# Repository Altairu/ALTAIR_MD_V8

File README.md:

# ALTAIR_MD_V8
**High-Power Isolated Motor Driver Board**

<blockquote class="twitter-tweet"><p lang="ja" dir="ltr">NEWもたどら <a href="https://t.co/xIfIAs8RRS">pic.twitter.com/xIfIAs8RRS</a></p>&mdash; -Altair- (@Flying___eagle) <a href="https://twitter.com/Flying___eagle/status/2016806401205797079?ref_src=twsrc%5Etfw">January 29, 2026</a></blockquote> 

## 概要 (Overview)
**ALTAIR_MD_V8** は、STMicroelectronics製の車載用高出力フルブリッジドライバー **VNH5019A-E** を搭載したDCモータードライバーモジュールです。

制御信号ラインにデジタルアイソレータ (**ADuM121N**) を採用することで、モーター駆動系（24V系）とマイコン制御系（3.3V/5V系）のGNDを完全に分離（絶縁）しています。

## 特徴 (Features)
*   **高出力駆動**: 連続12A / 最大30A の大電流駆動が可能（VNH5019A-E仕様に基づく）。
*   **完全絶縁設計**: Analog Devices製 デジタルアイソレータ ADuM121N を採用し、ロジック側とパワー側のGNDを分離。
*   **広範囲なロジック電圧**: 1.8V ～ 5V のロジック入力に対応（マイコンを選ばない設計）。
*   **保護機能**:
    *   過電圧・低電圧シャットダウン
    *   過熱保護 (Thermal Shutdown)
    *   電流センシング機能 (Current Sense Output)

## 仕様 (Specifications)

| 項目 | 仕様 | 備考 |
| :--- | :--- | :--- |
| **メインドライバー** | STMicroelectronics VNH5019A-E | AEC-Q100準拠 (車載グレード) |
| **絶縁素子** | Analog Devices ADuM121N | 2ch デジタルアイソレータ (計2個使用) |
| **入力電源電圧** | DC 5.5V ～ 24V | パワー側電源 (VCC/VBAT) |
| **ロジック入力電圧** | DC 1.8V ～ 5.5V | マイコン側I/O電圧 |
| **最大出力電流** | 連続 12A / ピーク 30A | 放熱条件に依存 |
| **電流センシング** | アナログ電圧出力 | 1.5kΩ抵抗接続時 (約0.14V/A) |

## 回路図 (Schematic)

### 主な構成
*   **絶縁回路**: マイコンからの制御信号（PWM1, PWM2, ENABLE）は、ADuM121N を介して VNH5019A-E に伝送されます。
*   **電源生成**: 24V入力からオンボードの降圧レギュレータにより、絶縁二次側（ドライバー側）用の5V電源を生成しています。
*   **保護設定**:
    *   **CP (Charge Pump)**: オープン（未接続）
    *   **VBAT**: VCCと短絡（逆接保護MOSFETなし構成のため）
  
## PCB Layout

## インターフェース (Interface)

### 入力ピン (CN1 / マイコン側)
| ピン名 | 機能 | 説明 |
| :--- | :--- | :--- |
| **PWM1** | INA 入力 | モーター回転方向制御 A (正転/逆転) |
| **PWM2** | INB 入力 | モーター回転方向制御 B (正転/逆転) |
| **SD** | 動作許可 (PWM Pin) | **HIGH**: 動作許可, **LOW**: フリーラン停止 (全OFF) |
| **GND** | ロジックGND | マイコン側のGNDと接続 |

### 出力ピン (CN2 / モーター・電源側)
| ピン名 | 機能 | 説明 |
| :--- | :--- | :--- |
| **+24V** | 電源入力 (+) | モーター用メイン電源 (最大24V) |
| **GND_P** | パワーGND (-) | 電源およびモーターのグラウンド |
| **OUT A** | モーター出力 A | モーターの端子へ接続 |
| **OUT B** | モーター出力 B | モーターの端子へ接続 |
| **CS** | 電流センス出力 | 電流値に応じたアナログ電圧を出力 (ADCで読取可) |

## 制御ロジック (Truth Table)

VNH5019A-E の仕様に基づく真理値表です。
**SD (Shutdown/Enable)** ピンが HIGH の時のみモーターが駆動します。

| SD (Enable) | PWM1 (INA) | PWM2 (INB) | OUT A | OUT B | 動作モード |
| :---: | :---: | :---: | :---: | :---: | :--- |
| **L** | X | X | OPEN | OPEN | **フリーラン停止 (All OFF)** |
| **H** | **H** | **L** | **H** | **L** | **正転 (CW)** |
| **H** | **L** | **H** | **L** | **H** | **逆転 (CCW)** |
| **H** | **L** | **L** | **L** | **L** | **ブレーキ (GNDショート)** |
| **H** | **H** | **H** | **H** | **H** | **ブレーキ (VCCショート)** |

*   速度制御を行う場合は、回転方向に応じて PWM1 または PWM2 に PWM信号を入力し、もう片方を LOW にしてください。
*   惰性走行させたい場合は、SDピンを LOW にしてください。

## 電流センシング (Current Sense)
CSピンからは、モーター電流に比例した電流が出力されます。基板上の 1.5kΩ 抵抗により電圧に変換されています。

*   **計算式**: $V_{CS} \approx \frac{I_{OUT}}{K} \times 1.5k\Omega$
*   **K係数**: Typ. 7000 (VNH5019A-E datasheet)
*   **目安**: モーター電流 1A あたり 約 0.21V の出力

## 組み立て・使用上の注意
1.  **電源投入順序**: 
    ロジック回路(ADuM121N)は一次側・二次側両方に電源が必要です。+24V電源を投入することで二次側5Vが生成され、システムが動作可能になります。
2.  **放熱**:
    30A近い電流を流す場合、IC底面の放熱パッド（ヒートスラッグ）への熱設計が重要です。必要に応じてヒートシンクや強制空冷を行ってください。
3.  **配線**:
    電源ラインとモーター出力ラインは、大電流が流れるため可能な限り太く短い配線を使用してください。

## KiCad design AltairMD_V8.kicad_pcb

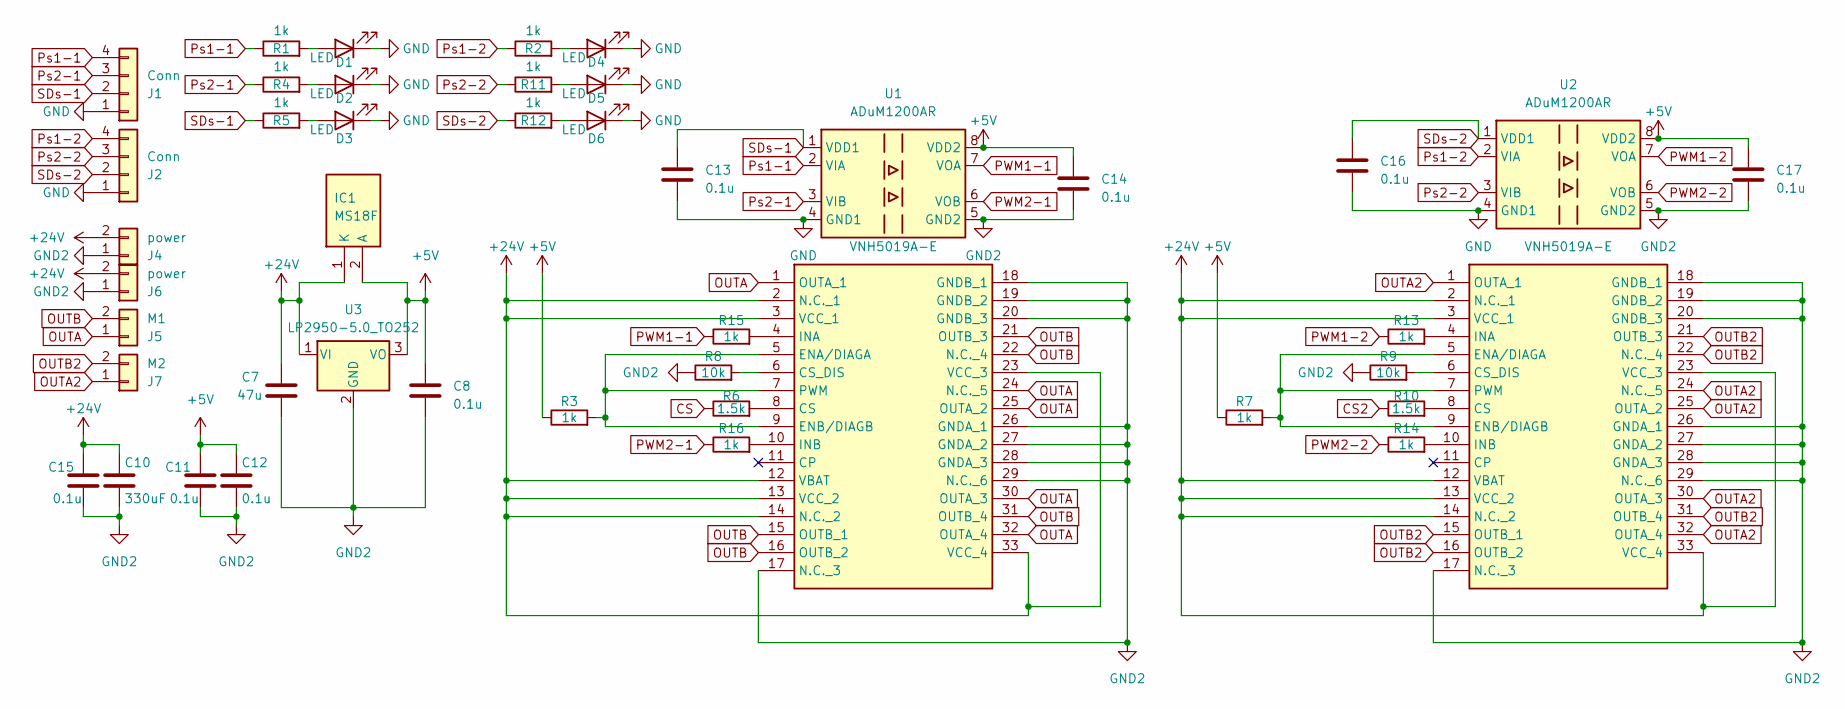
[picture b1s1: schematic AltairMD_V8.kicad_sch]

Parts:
C7: 47u; C_0603_1608Metric
C8, C11, C12, C13, C14, C15, C16, C17: 0.1u; C_0603_1608Metric
C10: 330uF; CP_Elec_10x10
D1, D2, D3, D4, D5, D6: LED; LED_0603_1608Metric
IC1: MS18F; SODFL4725X110N; Manufacturer_Part_Number MS18F
IC2, IC3: VNH5019A-E; VNH5019AE; Manufacturer_Part_Number VNH5019A-E; Mouser Part Number 511-VNH5019A-E
J1, J2: Conn; JST_XA_S04B-XASK-1_1x04_P2.50mm_Horizontal
J4, J6: power; AMASS_XT30PW-M_1x02_P2.50mm_Horizontal
J5: M1; AMASS_XT30PW-F_1x02_P2.50mm_Horizontal
J7: M2; AMASS_XT30PW-F_1x02_P2.50mm_Horizontal
R1, R2, R3, R4, R5, R7, R11, R12, R13, R14, R15, R16: 1k; R_0603_1608Metric
R6, R10: 1.5k; R_0603_1608Metric
R8, R9: 10k; R_0603_1608Metric
U1, U2: ADuM1200AR; SOIC-8_3.9x4.9mm_P1.27mm
U3: LP2950-5.0_TO252; TO-252-2

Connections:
+5V: C8.1, C11.1, C12.1, C14.1, C17.1, IC1.2 (A), R3.1, R7.1, U1.8 (VDD2), U2.8 (VDD2), U3.3 (VO)
+24V: C7.1, C10.1, C15.1, IC1.1 (K), IC2.2 (N.C._1), IC2.3 (VCC_1), IC2.12 (VBAT), IC2.13 (VCC_2), IC2.14 (N.C._2), IC2.23 (VCC_3), IC2.33 (VCC_4), IC3.2 (N.C._1), IC3.3 (VCC_1), IC3.12 (VBAT), IC3.13 (VCC_2), IC3.14 (N.C._2), IC3.23 (VCC_3), IC3.33 (VCC_4), J4.2, J6.2, U3.1 (VI)
CS: R6.1
CS2: R10.1
GND: C13.2, C16.2, D1.1 (K), D2.1 (K), D3.1 (K), D4.1 (K), D5.1 (K), D6.1 (K), J1.1, J2.1, U1.4 (GND1), U2.4 (GND1)
GND2: C7.2, C8.2, C10.2, C11.2, C12.2, C14.2, C15.2, C17.2, IC2.17 (N.C._3), IC2.18 (GNDB_1), IC2.19 (GNDB_2), IC2.20 (GNDB_3), IC2.26 (GNDA_1), IC2.27 (GNDA_2), IC2.28 (GNDA_3), IC2.29 (N.C._6), IC3.17 (N.C._3), IC3.18 (GNDB_1), IC3.19 (GNDB_2), IC3.20 (GNDB_3), IC3.26 (GNDA_1), IC3.27 (GNDA_2), IC3.28 (GNDA_3), IC3.29 (N.C._6), J4.1, J6.1, R8.1, R9.1, U1.5 (GND2), U2.5 (GND2), U3.2 (GND)
unnamed: D1.2 (A), R1.2
unnamed: D2.2 (A), R4.2
unnamed: D3.2 (A), R5.2
unnamed: D4.2 (A), R2.2
unnamed: D5.2 (A), R11.2
unnamed: D6.2 (A), R12.2
unnamed: IC2.8 (CS), R6.2
unnamed: IC2.6 (CS_DIS), R8.2
unnamed: IC2.5 (ENA/DIAGA), IC2.7 (PWM), IC2.9 (ENB/DIAGB), R3.2
unnamed: IC2.4 (INA), R15.2
unnamed: IC2.10 (INB), R16.2
unnamed: IC3.8 (CS), R10.2
unnamed: IC3.6 (CS_DIS), R9.2
unnamed: IC3.5 (ENA/DIAGA), IC3.7 (PWM), IC3.9 (ENB/DIAGB), R7.2
unnamed: IC3.4 (INA), R13.2
unnamed: IC3.10 (INB), R14.2
OUTA: IC2.1 (OUTA_1), IC2.24 (N.C._5), IC2.25 (OUTA_2), IC2.30 (OUTA_3), IC2.32 (OUTA_4), J5.1
OUTA2: IC3.1 (OUTA_1), IC3.24 (N.C._5), IC3.25 (OUTA_2), IC3.30 (OUTA_3), IC3.32 (OUTA_4), J7.1
OUTB: IC2.15 (OUTB_1), IC2.16 (OUTB_2), IC2.21 (OUTB_3), IC2.22 (N.C._4), IC2.31 (OUTB_4), J5.2
OUTB2: IC3.15 (OUTB_1), IC3.16 (OUTB_2), IC3.21 (OUTB_3), IC3.22 (N.C._4), IC3.31 (OUTB_4), J7.2
PWM1-1: R15.1, U1.7 (VOA)
PWM1-2: R13.1, U2.7 (VOA)
PWM2-1: R16.1, U1.6 (VOB)
PWM2-2: R14.1, U2.6 (VOB)
Ps1-1: J1.4, R1.1, U1.2 (VIA)
Ps1-2: J2.4, R2.1, U2.2 (VIA)
Ps2-1: J1.3, R4.1, U1.3 (VIB)
Ps2-2: J2.3, R11.1, U2.3 (VIB)
SDs-1: C13.1, J1.2, R5.1, U1.1 (VDD1)
SDs-2: C16.1, J2.2, R12.1, U2.1 (VDD1)

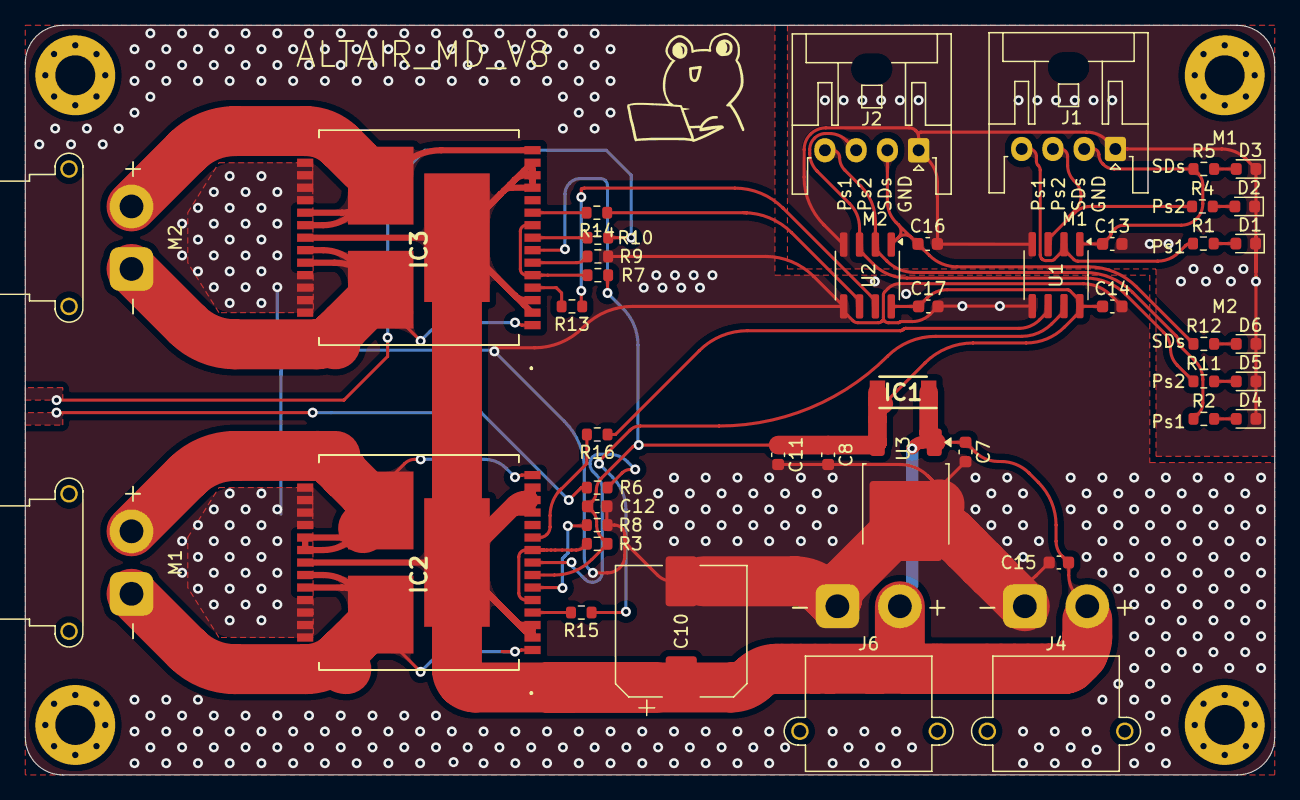
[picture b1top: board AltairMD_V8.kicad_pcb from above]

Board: 2 copper layers, 100.0 x 60.0 mm, 48 parts (0 on the bottom side), 34 nets.

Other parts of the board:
H1, H2, H3, H4: MountingHole; MountingHole_3.2mm_M3_Pad_Via

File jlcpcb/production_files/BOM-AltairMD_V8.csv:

Comment,Designator,Footprint,LCSC,Quantity
0.1u,"C11,C12,C13,C14,C15,C16,C17,C8",C_0603_1608Metric,C3011705,8
1.5k,"R10,R6",R_0603_1608Metric,C22843,2
10k,"R8,R9",R_0603_1608Metric,C15401,2
1k,"R1,R11,R12,R13,R14,R15,R16,R2,R3,R4,R5,R7",R_0603_1608Metric,C14676,12
330uF,C10,CP_Elec_10x10,C19606,1
47u,C7,C_0603_1608Metric,C140782,1
ADuM1200AR,"U1,U2",SOIC-8_3.9x4.9mm_P1.27mm,C660246,2
LED,"D1,D4",LED_0603_1608Metric,C2286,2
LED,"D2,D5",LED_0603_1608Metric,C2288,2
LED,"D3,D6",LED_0603_1608Metric,C2290,2
LP2950-5.0_TO252,U3,TO-252-2,C179571,1
MS18F,IC1,SODFL4725X110N,C60396,1
VNH5019A-E,"IC2,IC3",VNH5019AE,C2653552,2

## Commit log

2026-01-29 Refactor code structure for improved readability and maintainability
